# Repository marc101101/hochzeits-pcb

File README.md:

# hochzeits-pcb

Dieses Repository enthält ein KiCad-Projekt für eine kleine Hochzeits-PCB mit Knopfzelle, LED und Taster.
Neben den Projektdateien sind auch benutzerdefinierte Footprints im Ordner `blinkyparts.pretty` enthalten.

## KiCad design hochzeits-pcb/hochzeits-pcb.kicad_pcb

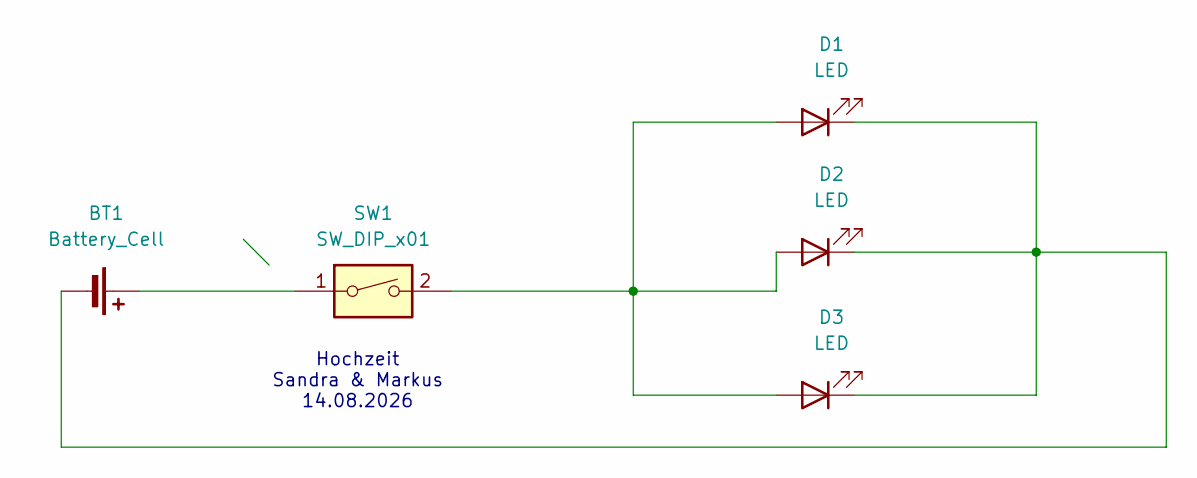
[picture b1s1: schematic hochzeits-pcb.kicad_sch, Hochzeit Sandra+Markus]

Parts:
BT1: Battery_Cell; BatteryHolder_Keystone_1060_1x2032_HandSoldering
D1, D2, D3: LED; D_3220_8050Metric_Pad2.65x5.15mm_HandSolder
SW1: SW_DIP_x01; Push_Button

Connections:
unnamed: BT1.1 (+), SW1.1
unnamed: BT1.2 (-), D1.1 (K), D2.1 (K), D3.1 (K)
unnamed: D1.2 (A), D2.2 (A), D3.2 (A), SW1.2

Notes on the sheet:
Hochzeit Sandra & Markus 14.08.2026

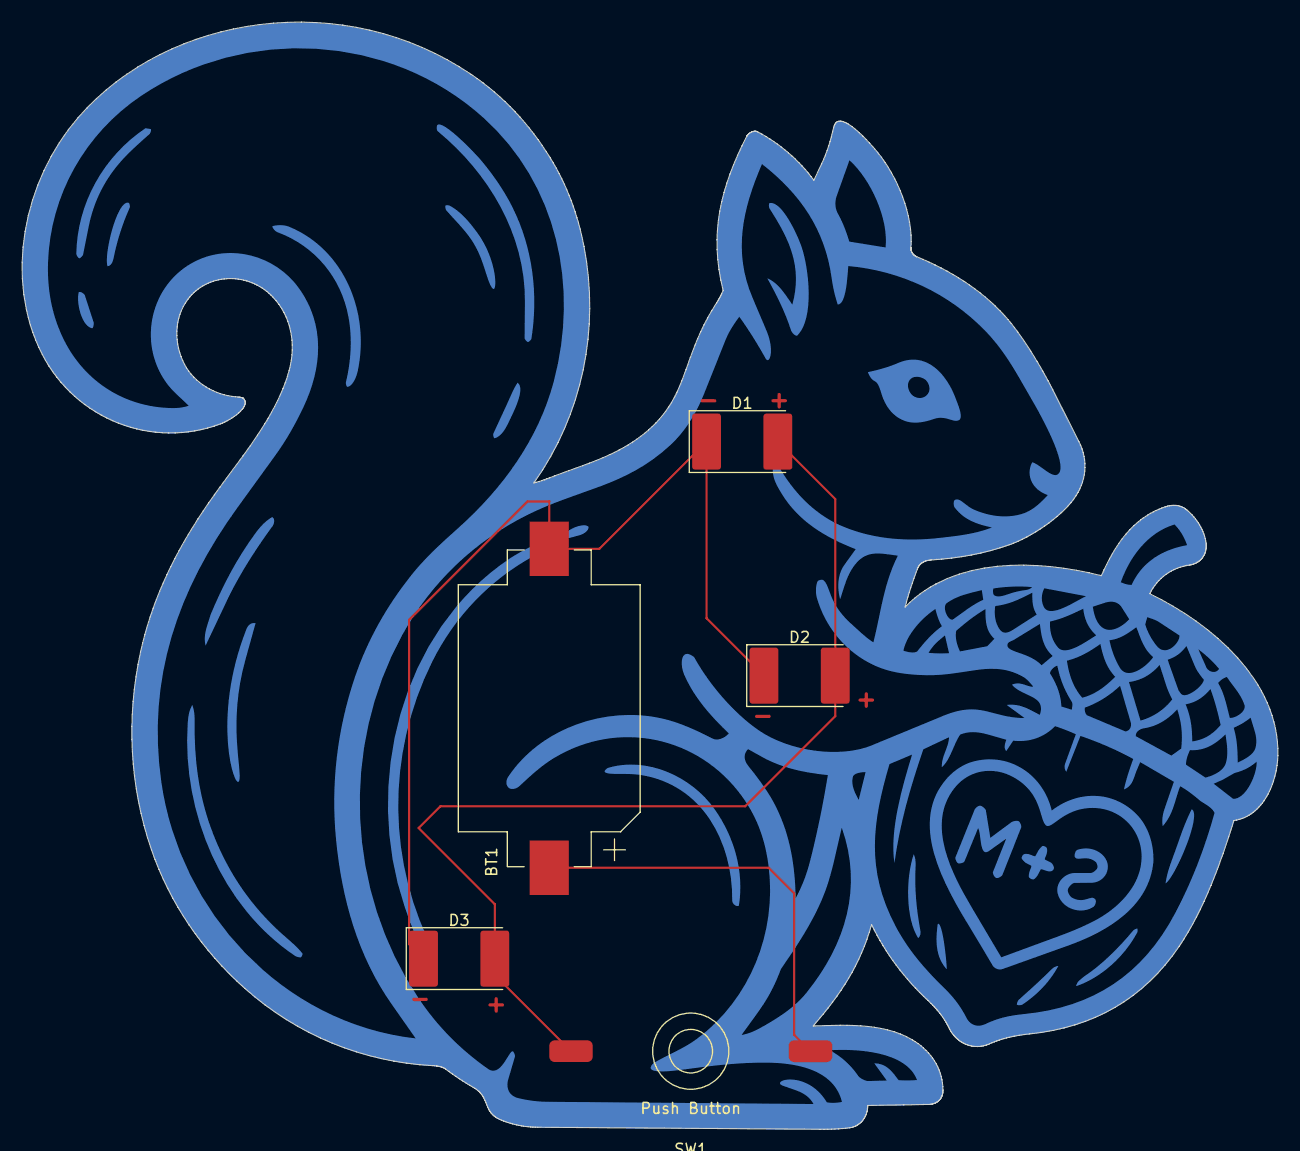
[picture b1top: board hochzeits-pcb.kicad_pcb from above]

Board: 2 copper layers, 115.4 x 101.7 mm, 5 parts (0 on the bottom side), 3 nets.

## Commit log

2026-05-17 feat: add lip + project
2026-05-17 Add README description and image
    Agent-Logs-Url: https://github.com/marc101101/hochzeits-pcb/sessions/36409383-dea2-4d98-a901-b36440db2402
2026-05-17 add image
2026-05-17 feat: add grafics
2026-05-17 feat: layout done
